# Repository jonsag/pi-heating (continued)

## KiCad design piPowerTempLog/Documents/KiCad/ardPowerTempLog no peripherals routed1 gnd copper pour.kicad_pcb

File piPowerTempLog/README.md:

piPowerTempLog  

A sub project to monitor power and temperatures  

Installing OS
=============================
Download Raspbian Stretch Lite from https://www.raspberrypi.org/downloads/raspbian/  
Choose the Light zip-file  

Cd to where your download is  
>$ unzip 2020-02-13-raspbian-buster-lite.zip  

Insert SD-card and find out drive letter  
>$ dmesg  

For example /dev/mmcblk0 or /dev/sdb  

Unmount if mounted  
>$ umount /dev/mmcblk0p1  

Write image to SD-card  
>$ sudo dd bs=4M if=2020-02-13-raspbian-buster-lite.img of=/dev/mmcblk0 conv=fsync status=progress 

Remove SD-card and insert it again to make new partitons visible     

Mount the first partition  
>$ sudo mount /dev/mmcblk0p1 /mnt/tmp  

Write empty file to boot partition to enable ssh at boot  
>$ sudo touch /mnt/tmp/ssh  

Remove SD-card and insert it a Rpi connected to your local network and boot it up  

Rpi configuration
-----------------------------
Connect to Rpi via ssh  
Login with user: pi and password:raspberry 

Update  
>$ sudo apt-get update && sudo apt-get upgrade  

Configure  
>$ sudo raspi-config   

1		Change password  
2 N1	Change hostname  
4 T1	Set locales  
4 T2	Set time zone  
4 T3	Choose keyboard layout    
4 T4	Set wifi country  
5 P7	Enable 1-wire at boot  
7 A1	Expand file system to use whole SD-card  
7 A3	Set memory split to 16  

Reboot to set new options  

Install LAMP
==========
Install packages  
>$ sudo apt install apache2 apache2-utils mariadb-server mariadb-client php php-mysql libapache2-mod-php php-common php-cli php-json php-readline

Check apache is running  
>$ systemctl status apache2

If not:
>$ sudo systemctl start apache2

>$ sudo systemctl enable apache2

Check MariaDB is running  
>$ systemctl status mariadb

If not:
>$ sudo systemctl start mariadb

>$ sudo systemctl enable mariadb

Run MariaDB post install script  
>$ sudo mysql_secure_installation

Set MariaDB root password  
Press 'enter'  to all remaining questions  

Test to connect to the db  
>$ sudo mysql -u root  

Enable the apache php mod  
>$ sudo a2enmod php7.3

Restart apache  
>$ sudo systemctl restart apache2

Test apache-php
----------
Create info.php in web root  
>$ sudo emacs /var/www/html/info.php

Put following in the file  

	<?php phpinfo(); ?>
	
Go to

	http://<raspberry pi's ip>/info.php
	
in a browser
	
Installation
==========
Install requisites
----------
>$ sudo apt install git rsync ttf-mscorefonts-installer

Other useful tools
----------
>$ sudo apt install emacs screen

Get source files
----------
>$ cd /home/pi  

>$ git clone https://github.com/jonsag/pi-heating.git  

>$ cd /home/pi/pi-heating/piPowerTempLog  

Setup database and user  
>$ sudo mysql -u root < database-setup.sql

Add tables to the new database  
>$ mysql -u arduino -parduinopass powerTempLog < tables-setup.sql

Copy contents of arduinolog to webroot  
>$ sudo cp -r piPowerTempLog /var/www/html/

Download calendar_localized and unzip it ( http://www.triconsole.com/php/calendar_datepicker.php)  
>$ sudo unzip calendar_localized* -d /var/www/html/piPowerTempLog/

Add symbolic links for fonts  
>$ cd /usr/share/fonts/truetype

>$ sudo ln -s msttcorefonts/arialbd.ttf arialbd.ttf

>$ sudo ln -s msttcorefonts/arial.ttf arial.ttf

Change ownership  
>$ sudo chown www-data:www-data -R /var/www/html

Add a line to your crontab  
>$ crontab -e

Add the following:  

	*/2 * * * * /usr/bin/php /var/www/html/piPowerTempLog/powerPoller.php 0 1 cron > /dev/null 2>&1
	*/2 * * * * /usr/bin/php /var/www/html/piPowerTempLog/tempPoller.php 0 1 cron > /dev/null 2>&1

Host settings
----------
Make sure your /etc/hosts has an entry for the arduino, for example:  

	192.168.10.10   arduino01

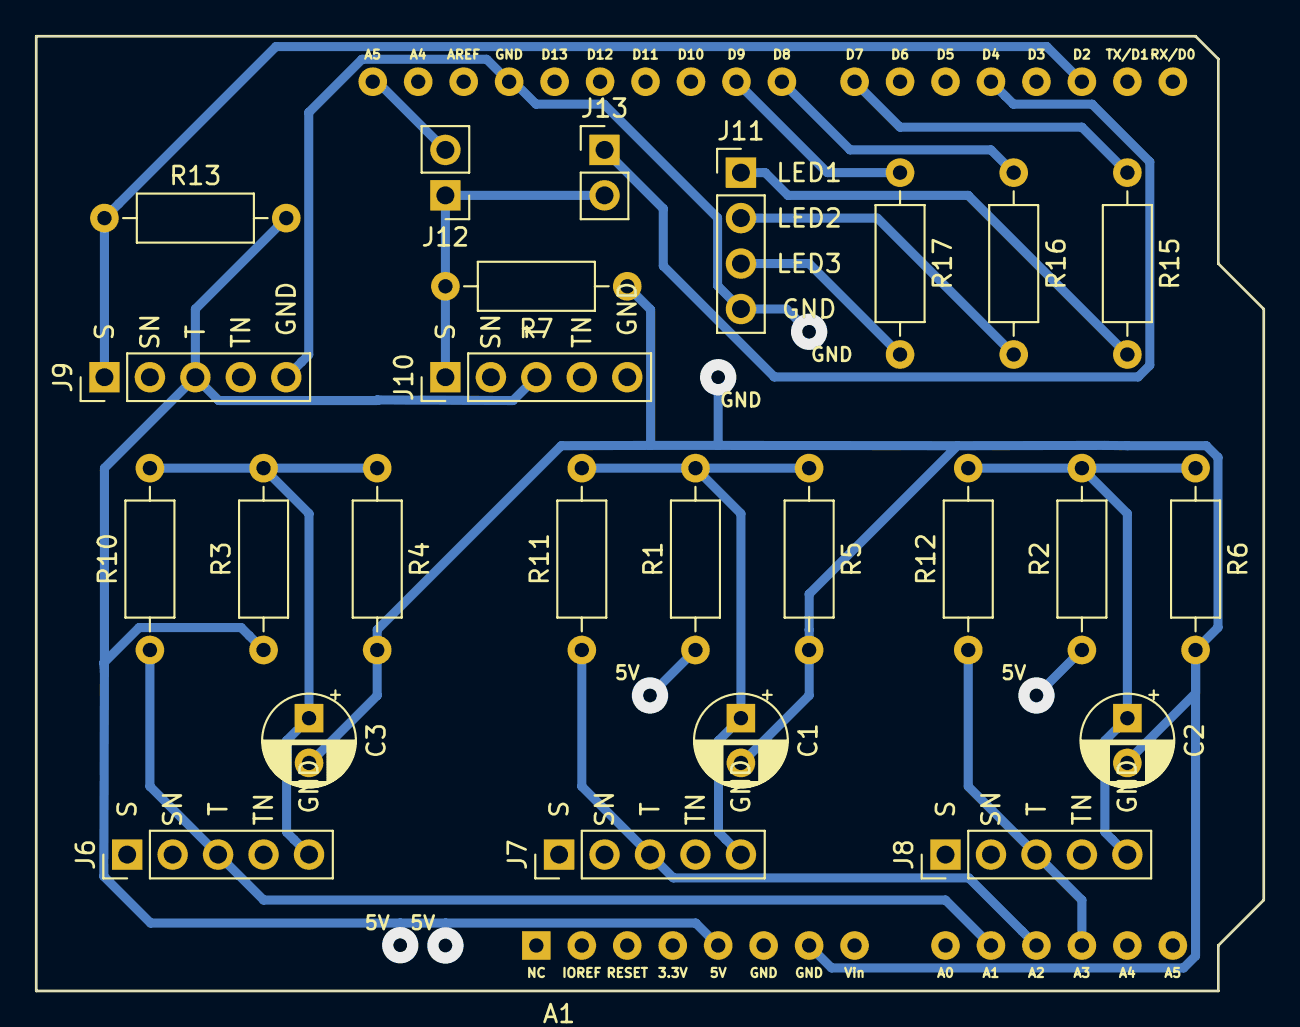
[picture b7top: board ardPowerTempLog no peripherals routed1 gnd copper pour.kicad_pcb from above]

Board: 2 copper layers, 68.6 x 53.3 mm, 26 parts (0 on the bottom side), 18 nets.

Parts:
A1: Arduino_UNO_R3; Arduino_UNO_R3_shield
C1, C2, C3: 10u; CP_Radial_D5.0mm_P2.50mm
J6, J7, J8, J9, J10: 5-pin_3-pole_3,5mm_audio_header; 5-pin_3,5mm_audio_jack_header
J11: 4-pin_3LED_header; 4-pin_3_LED_header
J12, J13: Conn_01x02_Male; PinHeader_1x02_P2.54mm_Vertical
R1, R2, R3, R4, R5, R6: 10k; R_Axial_DIN0207_L6.3mm_D2.5mm_P10.16mm_Horizontal
R7: 1k; R_Axial_DIN0207_L6.3mm_D2.5mm_P10.16mm_Horizontal
R10, R11, R12: 33R; R_Axial_DIN0207_L6.3mm_D2.5mm_P10.16mm_Horizontal
R13: 4.7k; R_Axial_DIN0207_L6.3mm_D2.5mm_P10.16mm_Horizontal
R15, R16, R17: 220R; R_Axial_DIN0207_L6.3mm_D2.5mm_P10.16mm_Horizontal

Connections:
/Collector: A1.5, J9.3, J10.3, R1.1, R2.1, R3.1, R13.2
/Data: A1.17, J9.1, R13.1
/Emitter: J10.1, J12.1, J13.2, R7.2
/GND: A1.7, A1.29, C1.2, C2.2, C3.2, J9.5, J11.4, R4.2, R5.2, R6.2, R7.1
unnamed: A1.10, J6.3, R10.1
unnamed: A1.11, J7.3, R11.1
unnamed: A1.12, J8.3, R12.1
unnamed: A1.19, J13.1
unnamed: A1.22, R15.1
unnamed: A1.23, R16.1
unnamed: A1.24, R17.1
unnamed: A1.32, J12.2
unnamed: C1.1, J7.5, R1.2, R5.1, R11.2
unnamed: C2.1, J8.5, R2.2, R6.1, R12.2
unnamed: C3.1, J6.5, R3.2, R4.1, R10.2
unnamed: J11.1, R15.2
unnamed: J11.2, R16.2
unnamed: J11.3, R17.2

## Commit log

2017-12-06 Deleted sh-scripts
2017-12-06 Paatched two files in www
2017-12-06 Second batch of files
2017-12-06 Third batch of files
2017-12-08 Renamed and included pi-heating-weather
2017-12-08 Added install for pi-heating-weather
2017-12-08 Correcting pi-heating-weather
2017-12-08 Correcting
2017-12-08 Now installing tables for weather
2017-12-08 Forgot a "
2017-12-09 Renamed some things
2017-12-09 Connect to db
2017-12-09 temperature.php and tempPoller.php now works
2017-12-13 Tinkered with temperature.php
2017-12-13 Changing some output
2017-12-15 now prints tempdata and draws temp chart
2017-12-17 Now polling power
2017-12-17 now draws current chart
2017-12-18 Now draws power/temp chart
2017-12-18 ... misc
2017-12-18 Added sketch for power measurements on arduino
2017-12-18 Added stuff and moved other stuff around
2017-12-19 Started working on weather
2017-12-19 Changed README
2017-12-20 Moved stuff around
2017-12-20 Weather installing
2017-12-20 Uploaded weather dir
2017-12-20 Now shows weather
2017-12-21 Added hub weather install
2017-12-21 Now logs and prints weather data
2017-12-21 Now creates csv from all tables
2018-01-04 Corrected mistake
2018-01-04 Corrected mistakes
2018-01-05 Sensors list now shows graph
2018-01-05 Messed around with some charts
2018-01-05 Cleaning up
2018-01-05 More cleaning
2018-01-08 Better charts
2018-01-10 How to connect LCD images
2018-01-10 New image and updated readme
2018-01-10 Deleted files
2018-01-10 Added symbols for gschem
2018-01-10 Files for LCD
2018-01-11 Uploaded gpio-watch
2018-01-11 Updated readme and added service script
2018-01-11 Added image and GPIO table
2018-01-11 Enabled LCD backlight control
2018-01-11 Fixed port bug when polling temps
2018-01-11 Button lights up LCD
2018-01-12 Outputs temp to LCD
2018-01-13 Testing symbolic link in git
2018-01-13 Switched to symlinks for gpio
2018-01-13 Added image. Cahnged gpio scripts
2018-01-13 Added buttons 2,3 and 4
2018-01-13 Added new symbolic links
2018-01-13 Redid links
2018-01-16 4 buttons work
2018-01-28 LCD-updates
2018-01-28 LCD now prints degree sign
2018-02-04 New output to LCD
2018-02-04 Bugs
2018-02-04 Strange bug in modules... Will look into it later
2018-02-20 Updated Arduino Logger sketch
2018-11-02 README tweaks
2018-11-25 Added script to calculate ideal burden resisto for the CT sensor
2018-12-06 Updated Readme. Added small scripts for calculating burden resistor when measuring currents for power logging.
2019-02-20 updates...
2019-02-20 corr...
2020-02-09 added KiCad
2020-02-15 kicad
2020-02-21 schematics
2020-02-21 added text
2020-02-22 added new arduino sketch for current temp logging
2020-02-22 added sub project, moved stuff around
2020-02-22 deleted old
2020-02-22 added powerTempLog
2020-02-22 updated jpgraph
2020-02-22 updated calendar
2020-02-22 updated to mysqli
2020-02-22 added older powertemplog
2020-02-22 deleted calendar directory
2020-02-22 many changes
2020-02-22 changed mysql_ to mysqli_
2020-02-22 starting the work upgrading to mysqli
2020-02-22 changed table
2020-02-22 mysqli updates
2020-02-22 GUI updates
2020-02-23 cleaned up
2020-02-23 more moving
2020-02-24 updating installation and instructions
2020-02-25 updated install script
2020-02-25 updated references
2020-02-25 pi heating remote updates
2020-02-25 updated piHeatingLCD
2020-02-26 renaming
2020-02-27 added schematcs and pcb, changed gpio
2020-02-29 kicad for rpi1
2020-02-29 updated install, added uninstall
2020-02-29 more info
2020-02-29 nicer
2020-02-29 even nicer
2020-02-29 better
2020-02-29 better service check
2020-03-01 updated uninstall
2020-03-01 updated install
2020-03-01 updated installs
2020-03-01 upd uninst
2020-03-01 better cad
2020-03-01 many ...
2020-03-01 more deletes
2020-03-01 moved LCD files
2020-03-01 organizing
2020-03-01 deleting and updating
2020-03-04 added comment
2020-03-07 updated kicad
2020-03-09 added resistor value in kicad
2020-03-09 added more kicad files
2020-03-09 moved dallas from 5V to 3.3V
2020-03-14 changed www installation path (once again...)
2020-03-14 disabled SQL strict mode, updated README
2020-03-14 cleaned up README
2020-03-15 LCD now working, started work on powerTempLog
2020-03-15 now prints tables, power and temp charts, not all powertemp chart
2020-03-15 currents and powertemp chart, csv working
2020-03-16 prettyfied www
2020-03-16 started work on ardWeatherStation
2020-03-16 KiCad start
2020-03-17 arduino weather
2020-03-17 kicad: connector for weather sensors
2020-03-18 kicad weather meters
2020-03-18 kicad weather
2020-03-18 kicad, PCB
2020-03-18 addded LCD BackPack
2020-03-22 weather sketch updates
2020-03-22 weather sketch
2020-03-24 piWeather working
2020-03-26 started on an unified install script
2020-03-28 bug, install script makes mistakes finding installed packages, not fixed
2020-03-28 install.sh now installs piHeatingHub
2020-03-28 Readme
2020-03-28 now installs everything, post install just does minor checking
2020-03-29 bug when creating crons, moved around documentation
2020-03-29 moved around sketches
2020-03-29 updated tc_calendar, not working properly at the moment
2020-03-29 updated install and uninstall
2020-03-29 completed post install check, new cron jobs, tidied up installs
2020-03-29 updated powerTempLog sketch
2020-03-29 images
2020-03-29 added some images to README
2020-03-29 README update, deletions
2020-03-30 tty session not starting in piWeather
2020-03-30 piWeatherLog now starts tty session at boot
2020-03-30 various bugs and tidying
2020-04-01 removed temp reading from ardPowerTempLog
2020-04-02 prettyfying outputs
2020-04-11 ardPowerTempLog sketch update
2020-07-08 added nodeMCU remote
2020-07-09 added sketch to discover dallas 1-wire devices (DS18B20)
2020-07-11 dallas temp web server
2020-07-11 now displays values for pi heating hub
2020-07-12 nodemcu ds18b20 now works
2021-01-27 line feeds
2021-01-30 formatting
2021-11-05 formatted
2021-11-06 Readme n install
2021-11-06 ->Python3, new install routines
2021-11-07 bashrc replacements
2021-11-08 Update README.md
    https://forum.kicad.info/t/warning-avoid-all-links-to-kicad-pcb-org-use-kicad-org/31521
2021-11-08 bashrc n python
2021-11-29 Creaated PlatformIO projects
2021-11-29 Deleted old sketches
2021-11-29 formats
2022-05-14 ardPowerTempLog schematics
2022-05-14 kicad ardWeatherStation
2022-05-16 Rasp n moves
2025-02-09 cleanup
2025-02-09 kicad v8
